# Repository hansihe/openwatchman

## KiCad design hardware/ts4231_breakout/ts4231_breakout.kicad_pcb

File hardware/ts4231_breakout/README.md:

# TS4231 ASIC breakout board

Made this because the ones triad makes are too expensive!

The TS4231 is availible relatively easily from Triad: https://www.triadsemi.com/product/ts4231/

Although the ASIC BGA is fairly small, it's not very difficult to solder with hot air.

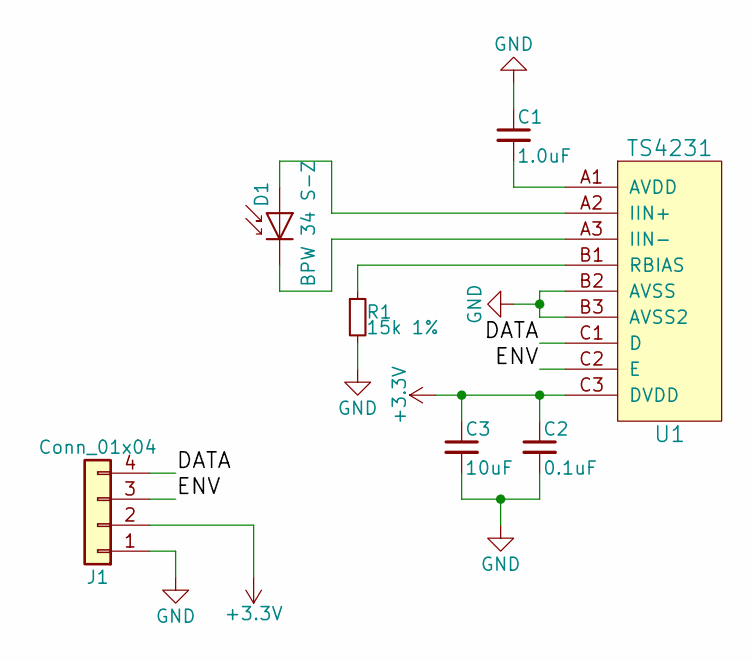
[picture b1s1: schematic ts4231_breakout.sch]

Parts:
C1: 1.0uF; C_0603
C2: 0.1uF; C_0603
C3: 10uF; C_0603
D1: BPW 34 S-Z; PhotoDiode_SMD-DIL2_4.5x4
J1: Conn_01x04; Pin_Header_Angled_1x04_Pitch2.54mm
R1: 15k 1%; R_0603
U1: TS4231; WLCSP-3x3

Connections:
+3V3: C2.1, C3.1, J1.2, U1.C3 (DVDD)
/DATA: J1.4, U1.C1 (D)
/ENV: J1.3, U1.C2 (E)
GND: C1.1, C2.2, C3.2, J1.1, R1.2, U1.B2 (AVSS), U1.B3 (AVSS2)
unnamed: C1.2, U1.A1 (AVDD)
unnamed: D1.1 (K), U1.A3 (IIN-)
unnamed: D1.2 (A), U1.A2 (IIN+)
unnamed: R1.1, U1.B1 (RBIAS)

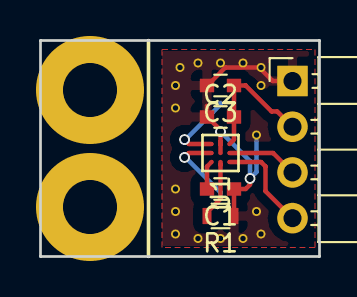
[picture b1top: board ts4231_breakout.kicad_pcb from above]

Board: 2 copper layers, 15.5 x 12.0 mm, 7 parts (1 on the bottom side), 8 nets.

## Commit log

2020-09-13 Add notebooks
